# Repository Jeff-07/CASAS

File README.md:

# CASAS
ECE 23-013 Capstone Design Codes, Programs, and Designs

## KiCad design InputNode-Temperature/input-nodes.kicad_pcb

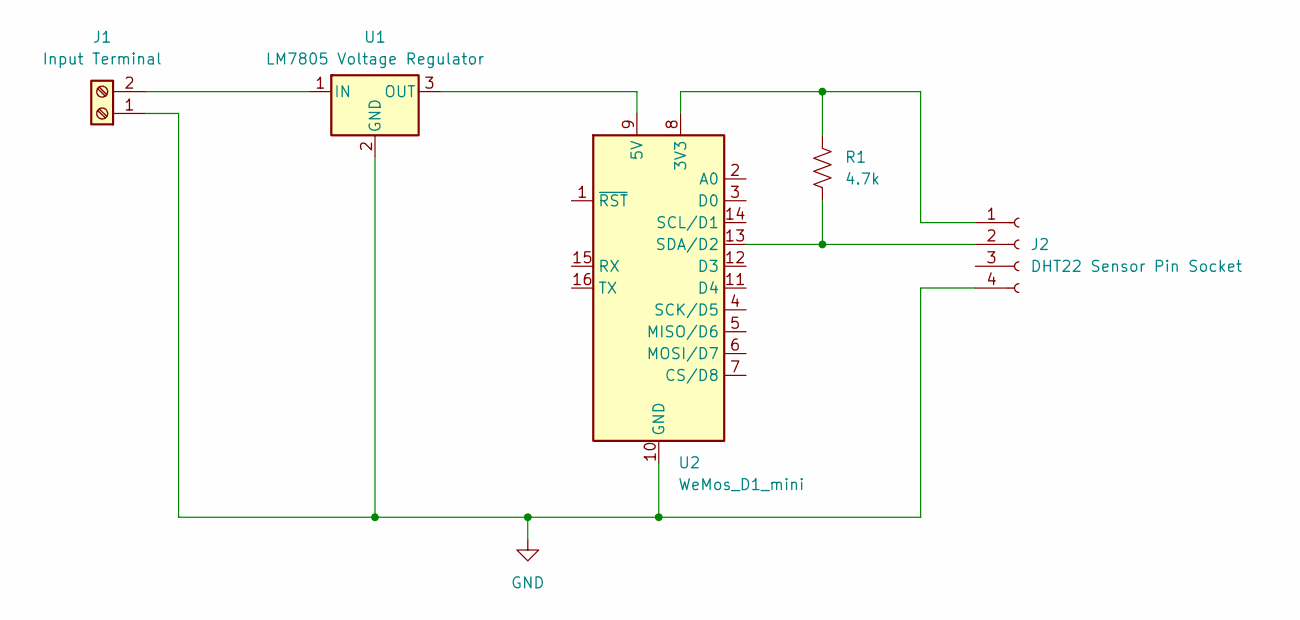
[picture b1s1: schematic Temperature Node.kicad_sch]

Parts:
J1: Input Terminal; TerminalBlock_Phoenix_MKDS-1,5-2_1x02_P5.00mm_Horizontal
J2: DHT22 Sensor Pin Socket; PinSocket_1x04_P1.00mm_Vertical
R1: 4.7k; R_Axial_DIN0207_L6.3mm_D2.5mm_P10.16mm_Horizontal
U1: LM7805 Voltage Regulator; TO-220-3_Horizontal_TabDown
U2: WeMos_D1_mini; WEMOS_D1_mini_light

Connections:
GND: J1.1, J2.4, U1.2 (GND), U2.10 (GND)
unnamed: J1.2, U1.1 (IN)
unnamed: J2.1, R1.1, U2.8 (3V3)
unnamed: J2.2, R1.2, U2.13 (SDA/D2)
unnamed: U1.3 (OUT), U2.9 (5V)

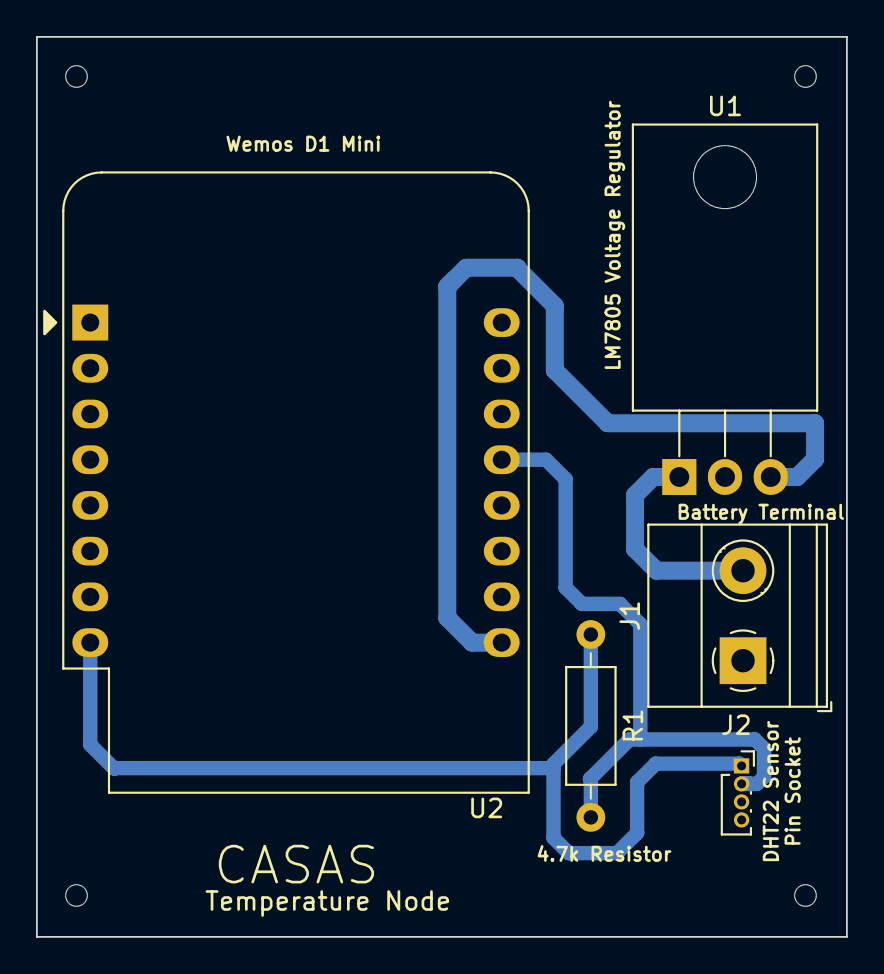
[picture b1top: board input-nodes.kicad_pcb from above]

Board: 2 copper layers, 45.0 x 50.0 mm, 5 parts (0 on the bottom side), 5 nets.

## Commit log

2024-05-18 Create hello
